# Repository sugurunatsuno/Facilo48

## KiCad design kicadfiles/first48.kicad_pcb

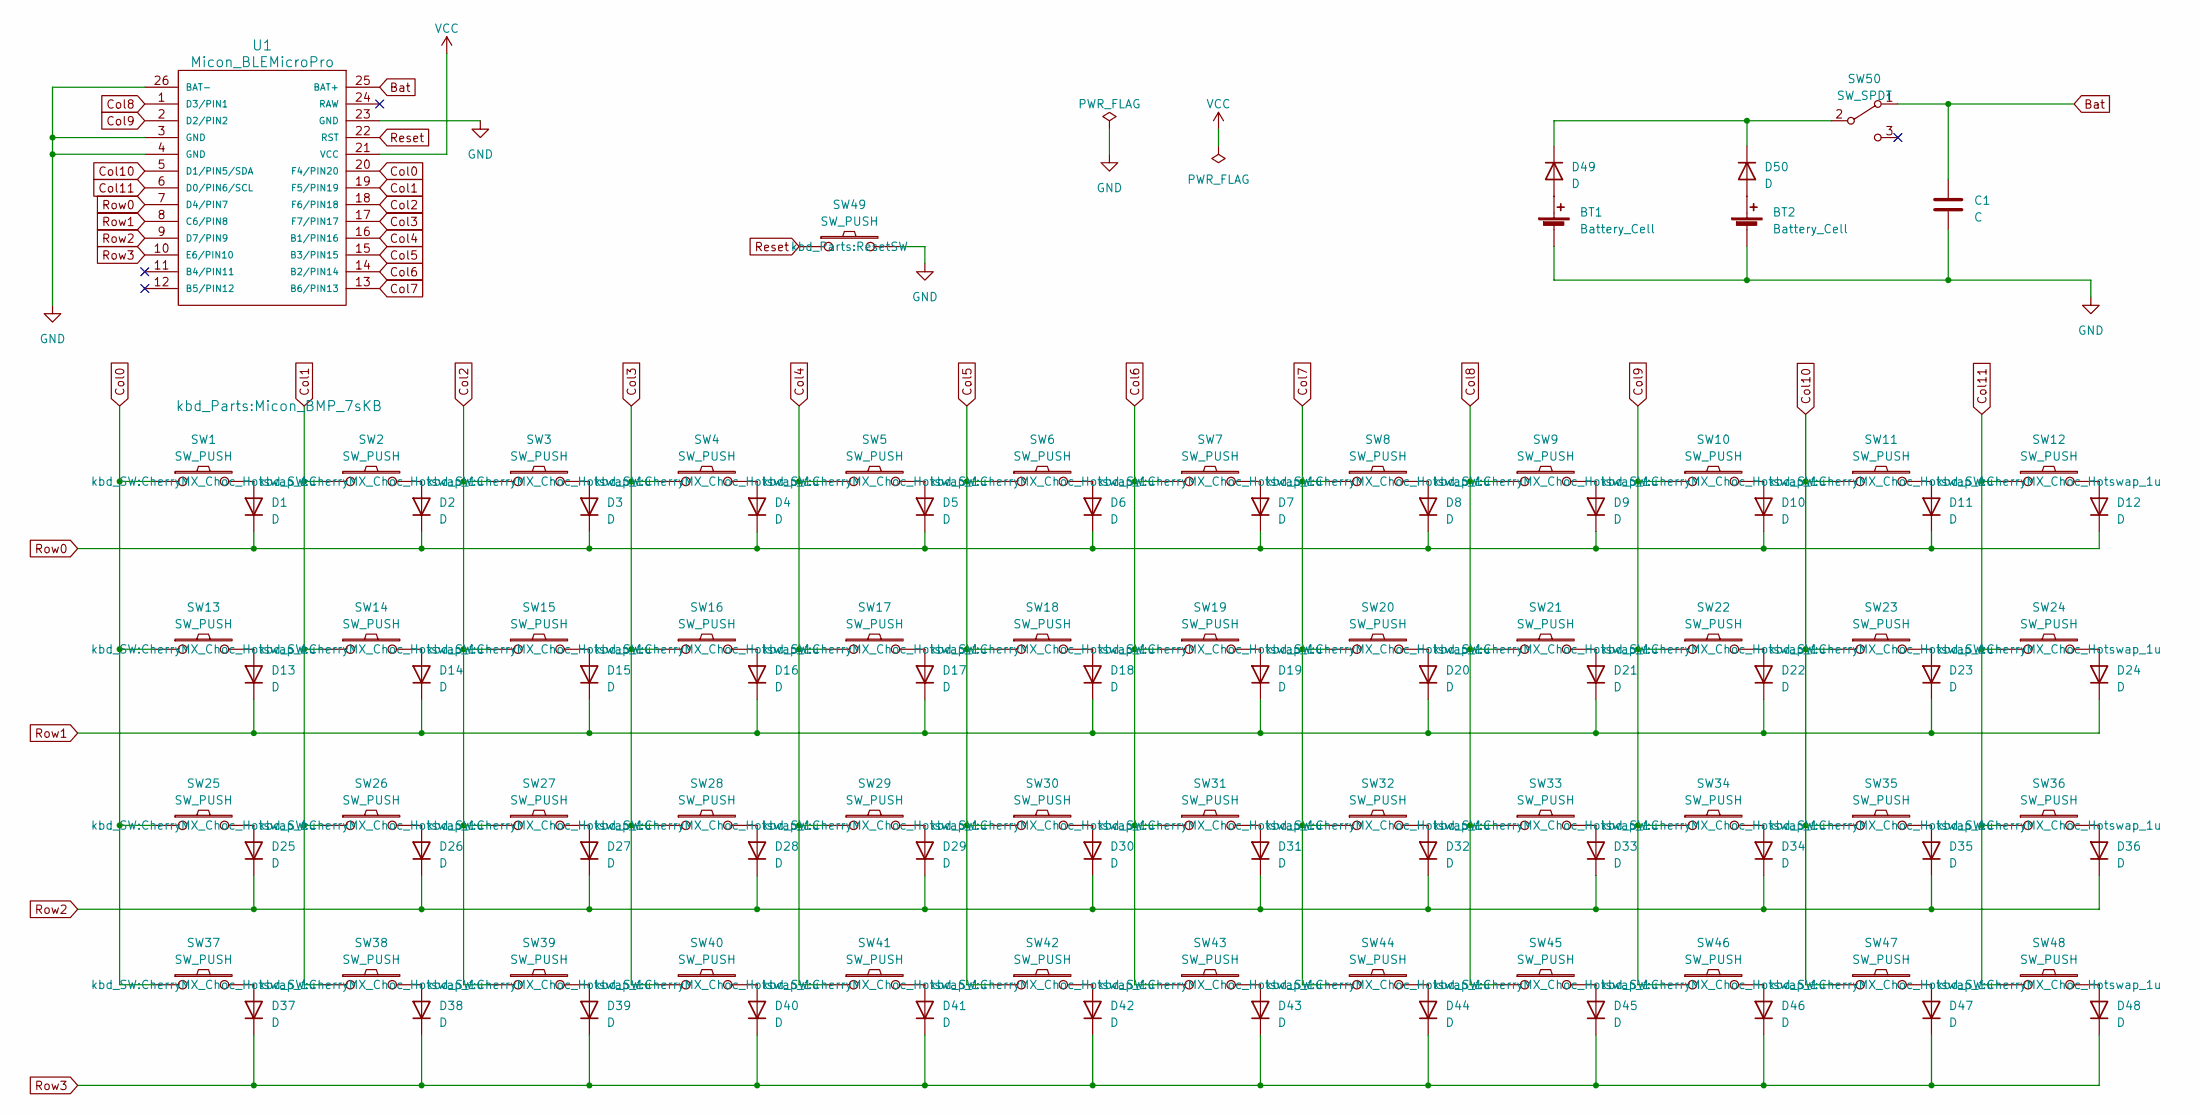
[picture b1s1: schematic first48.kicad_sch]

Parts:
BT1, BT2: Battery_Cell; Battery_ali_CR1632
C1: C; Capacitor_1206
D1, D2, D3, D4, D5, D6, D7, D8, D9, D10, D11, D12, D13, D14, D15, D16, D17, D18, D19, D20, D21, D22, D23, D24, D25, D26, D27, D28, D29, D30, D31, D32, D33, D34, D35, D36, D37, D38, D39, D40, D41, D42, D43, D44, D45, D46, D47, D48, D49, D50: D; Diode_SMD
SW1, SW2, SW3, SW4, SW5, SW6, SW7, SW8, SW9, SW10, SW11, SW12, SW13, SW14, SW15, SW16, SW17, SW18, SW19, SW20, SW21, SW22, SW23, SW24, SW25, SW26, SW27, SW28, SW29, SW30, SW31, SW32, SW33, SW34, SW35, SW36, SW37, SW38, SW39, SW40, SW41, SW42, SW43, SW44, SW45, SW46, SW47, SW48: SW_PUSH; CherryMX_Choc_Hotswap_1u
SW49: SW_PUSH; ResetSW
SW50: SW_SPDT; TGSW_MSK-12D19
U1: Micon_BLEMicroPro; Micon_BMP_7sKB

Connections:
Bat: C1.1, SW50.1 (A), U1.25 (BAT+)
Col0: SW1.1, SW13.1, SW25.1, SW37.1, U1.20 (F4/PIN20)
Col1: SW2.1, SW14.1, SW26.1, SW38.1, U1.19 (F5/PIN19)
Col2: SW3.1, SW15.1, SW27.1, SW39.1, U1.18 (F6/PIN18)
Col3: SW4.1, SW16.1, SW28.1, SW40.1, U1.17 (F7/PIN17)
Col4: SW5.1, SW17.1, SW29.1, SW41.1, U1.16 (B1/PIN16)
Col5: SW6.1, SW18.1, SW30.1, SW42.1, U1.15 (B3/PIN15)
Col6: SW7.1, SW19.1, SW31.1, SW43.1, U1.14 (B2/PIN14)
Col7: SW8.1, SW20.1, SW32.1, SW44.1, U1.13 (B6/PIN13)
Col8: SW9.1, SW21.1, SW33.1, SW45.1, U1.1 (D3/PIN1)
Col9: SW10.1, SW22.1, SW34.1, SW46.1, U1.2 (D2/PIN2)
Col10: SW11.1, SW23.1, SW35.1, SW47.1, U1.5 (D1/PIN5/SDA)
Col11: SW12.1, SW24.1, SW36.1, SW48.1, U1.6 (D0/PIN6/SCL)
GND: BT1.2 (-), BT2.2 (-), C1.2, SW49.2, U1.3 (GND), U1.4 (GND), U1.23 (GND), U1.26 (BAT-)
unnamed: BT1.1 (+), D49.2 (A)
unnamed: BT2.1 (+), D50.2 (A)
unnamed: D1.2 (A), SW1.2
unnamed: D2.2 (A), SW2.2
unnamed: D3.2 (A), SW3.2
unnamed: D4.2 (A), SW4.2
unnamed: D5.2 (A), SW5.2
unnamed: D6.2 (A), SW6.2
unnamed: D7.2 (A), SW7.2
unnamed: D8.2 (A), SW8.2
unnamed: D9.2 (A), SW9.2
unnamed: D10.2 (A), SW10.2
unnamed: D11.2 (A), SW11.2
unnamed: D12.2 (A), SW12.2
unnamed: D13.2 (A), SW13.2
unnamed: D14.2 (A), SW14.2
unnamed: D15.2 (A), SW15.2
unnamed: D16.2 (A), SW16.2
unnamed: D17.2 (A), SW17.2
unnamed: D18.2 (A), SW18.2
unnamed: D19.2 (A), SW19.2
unnamed: D20.2 (A), SW20.2
unnamed: D21.2 (A), SW21.2
unnamed: D22.2 (A), SW22.2
unnamed: D23.2 (A), SW23.2
unnamed: D24.2 (A), SW24.2
unnamed: D25.2 (A), SW25.2
unnamed: D26.2 (A), SW26.2
unnamed: D27.2 (A), SW27.2
unnamed: D28.2 (A), SW28.2
unnamed: D29.2 (A), SW29.2
unnamed: D30.2 (A), SW30.2
unnamed: D31.2 (A), SW31.2
unnamed: D32.2 (A), SW32.2
unnamed: D33.2 (A), SW33.2
unnamed: D34.2 (A), SW34.2
unnamed: D35.2 (A), SW35.2
unnamed: D36.2 (A), SW36.2
unnamed: D37.2 (A), SW37.2
unnamed: D38.2 (A), SW38.2
unnamed: D39.2 (A), SW39.2
unnamed: D40.2 (A), SW40.2
unnamed: D41.2 (A), SW41.2
unnamed: D42.2 (A), SW42.2
unnamed: D43.2 (A), SW43.2
unnamed: D44.2 (A), SW44.2
unnamed: D45.2 (A), SW45.2
unnamed: D46.2 (A), SW46.2
unnamed: D47.2 (A), SW47.2
unnamed: D48.2 (A), SW48.2
unnamed: D49.1 (K), D50.1 (K), SW50.2 (B)
Reset: SW49.1, U1.22 (RST)
Row0: D1.1 (K), D2.1 (K), D3.1 (K), D4.1 (K), D5.1 (K), D6.1 (K), D7.1 (K), D8.1 (K), D9.1 (K), D10.1 (K), D11.1 (K), D12.1 (K), U1.7 (D4/PIN7)
Row1: D13.1 (K), D14.1 (K), D15.1 (K), D16.1 (K), D17.1 (K), D18.1 (K), D19.1 (K), D20.1 (K), D21.1 (K), D22.1 (K), D23.1 (K), D24.1 (K), U1.8 (C6/PIN8)
Row2: D25.1 (K), D26.1 (K), D27.1 (K), D28.1 (K), D29.1 (K), D30.1 (K), D31.1 (K), D32.1 (K), D33.1 (K), D34.1 (K), D35.1 (K), D36.1 (K), U1.9 (D7/PIN9)
Row3: D37.1 (K), D38.1 (K), D39.1 (K), D40.1 (K), D41.1 (K), D42.1 (K), D43.1 (K), D44.1 (K), D45.1 (K), D46.1 (K), D47.1 (K), D48.1 (K), U1.10 (E6/PIN10)
VCC: U1.21 (VCC)

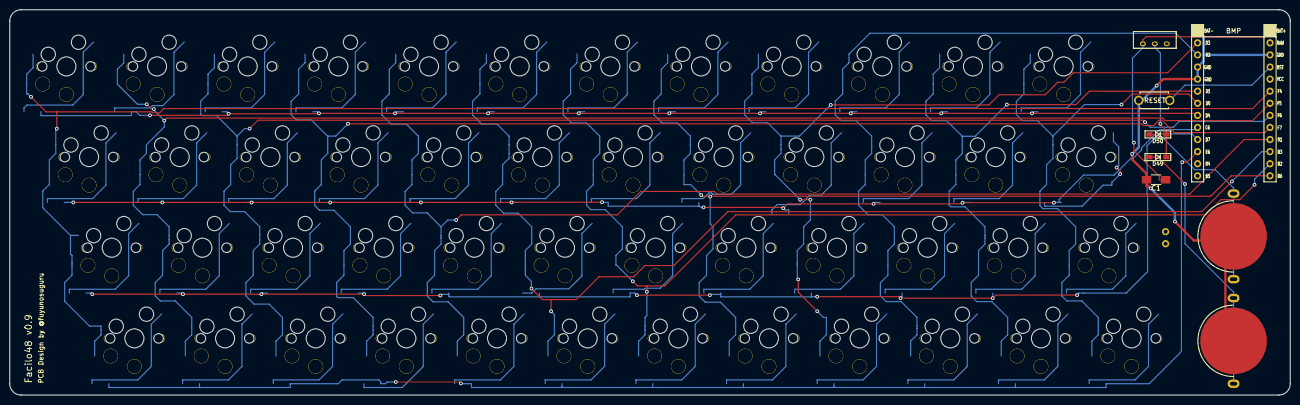
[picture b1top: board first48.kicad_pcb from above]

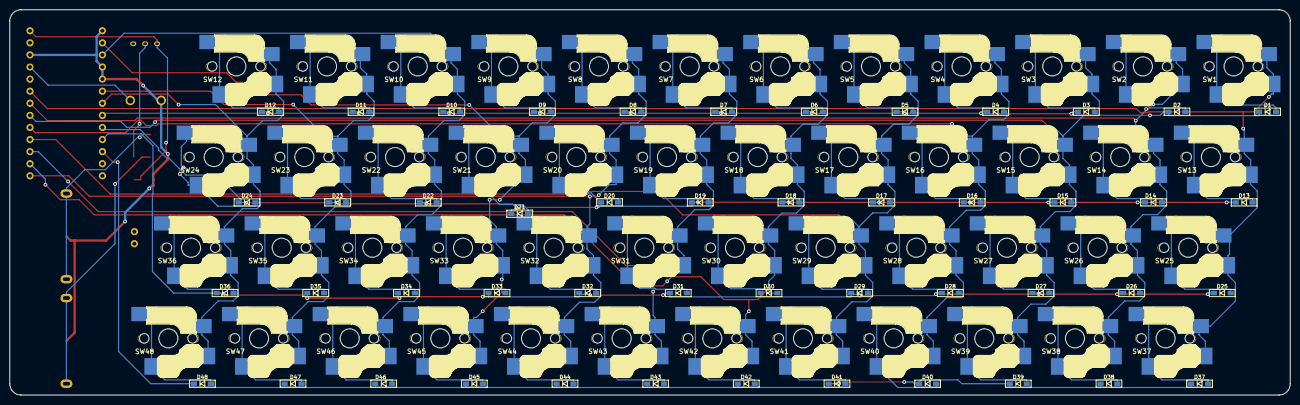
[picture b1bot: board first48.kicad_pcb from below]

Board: 2 copper layers, 269.1 x 81.0 mm, 105 parts (3 on the bottom side), 70 nets.

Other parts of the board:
J2: Conn_01x02; Battery_BMP_2pin

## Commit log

2023-04-08 ファイル追加
